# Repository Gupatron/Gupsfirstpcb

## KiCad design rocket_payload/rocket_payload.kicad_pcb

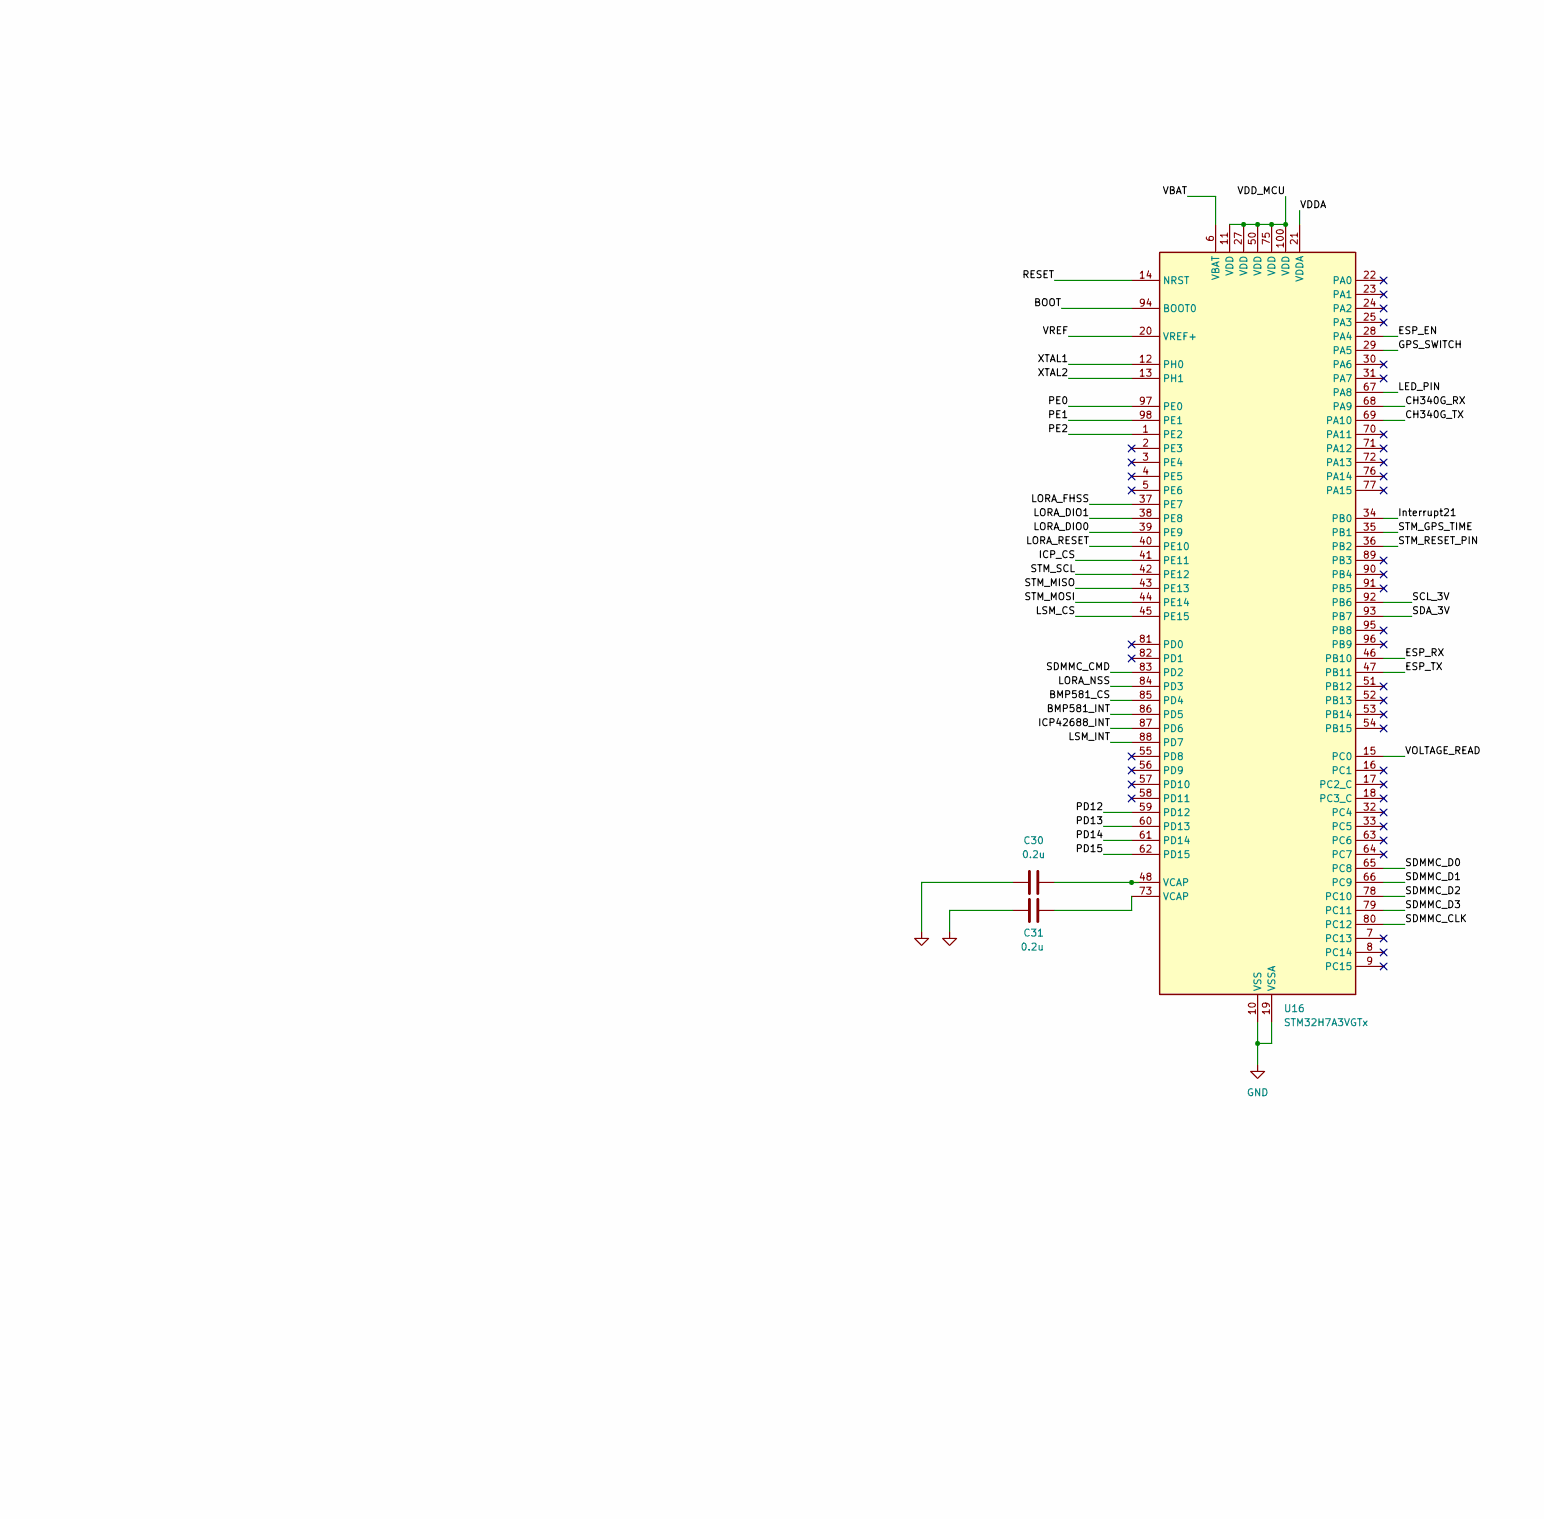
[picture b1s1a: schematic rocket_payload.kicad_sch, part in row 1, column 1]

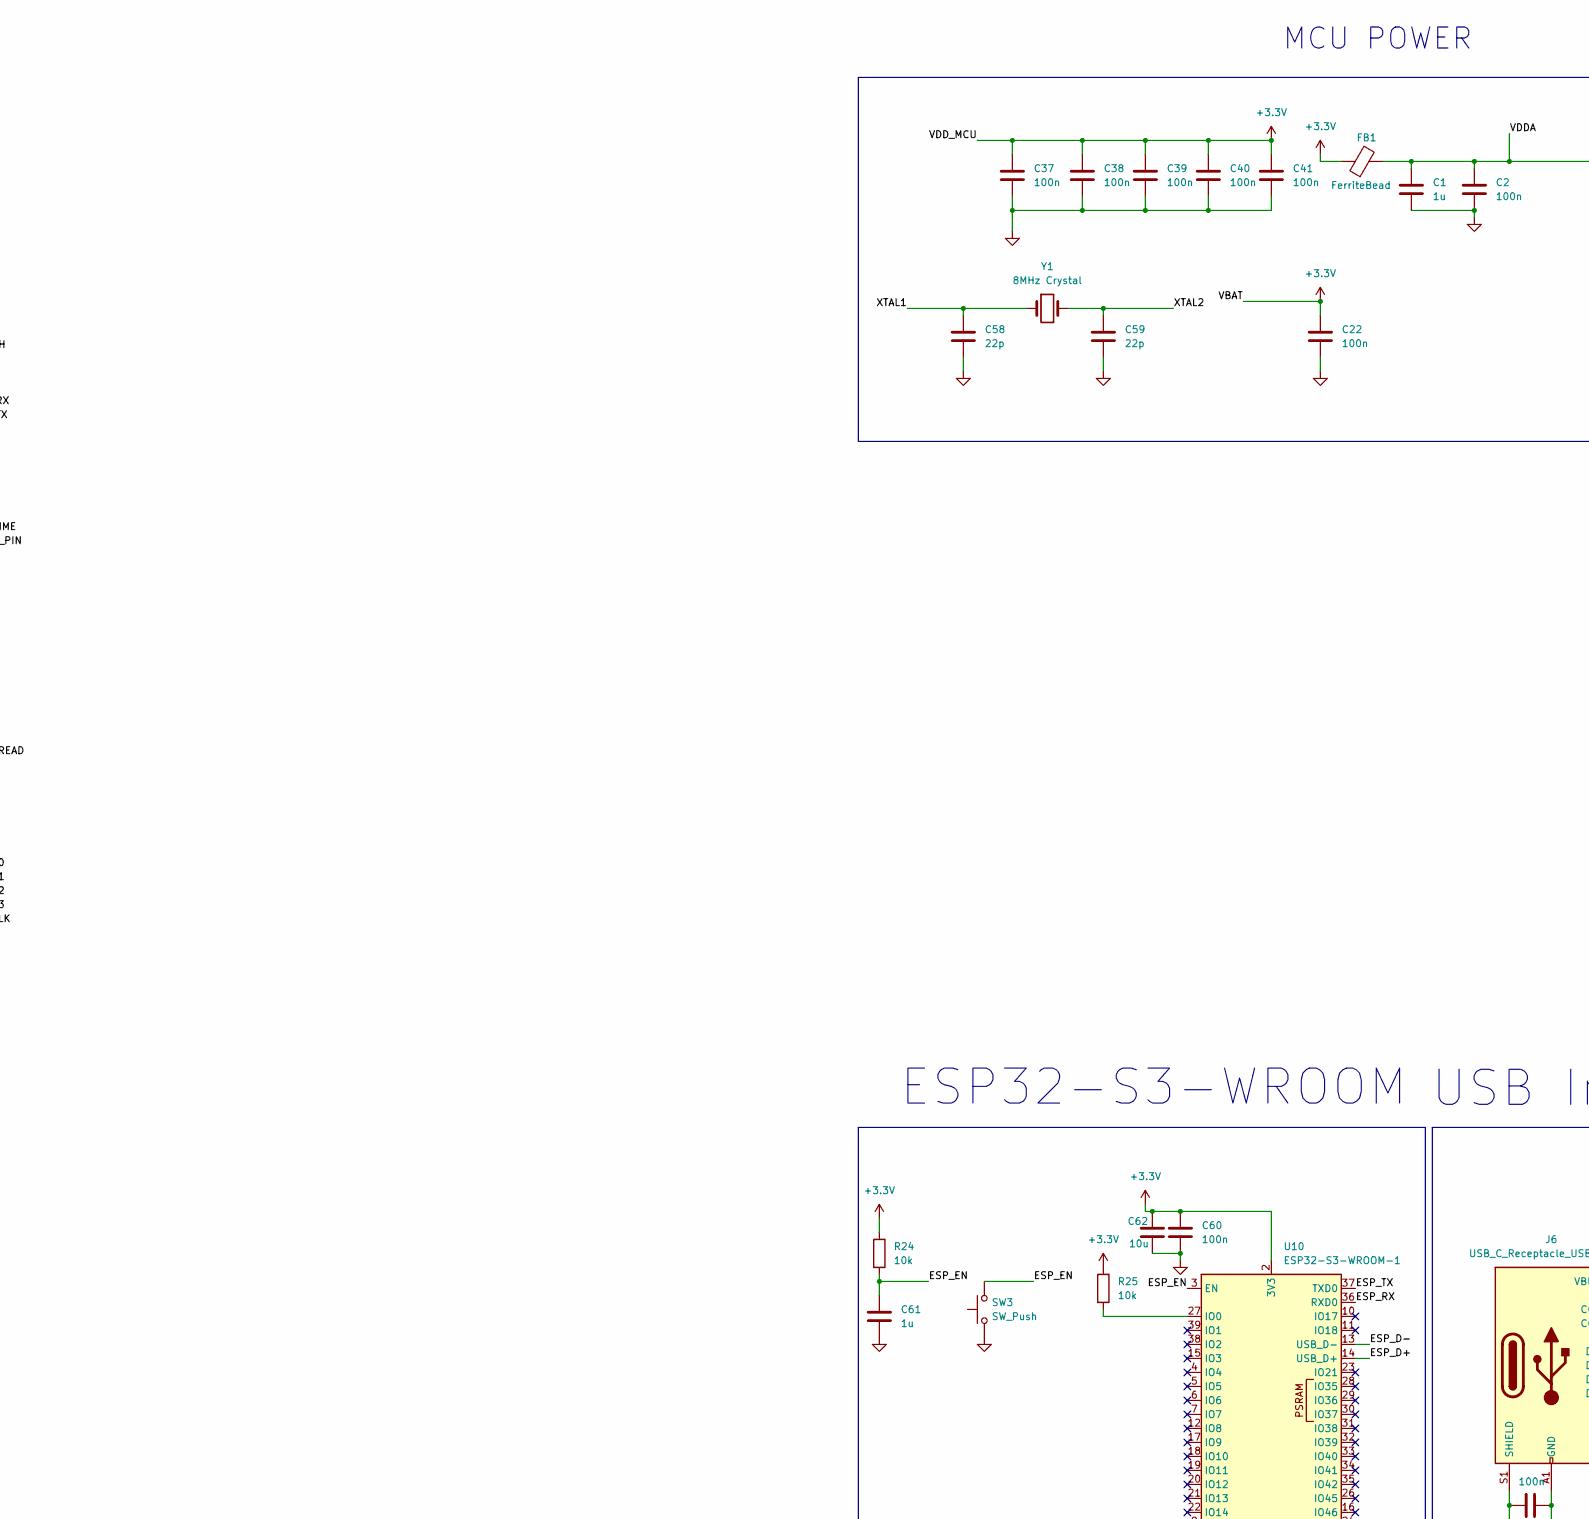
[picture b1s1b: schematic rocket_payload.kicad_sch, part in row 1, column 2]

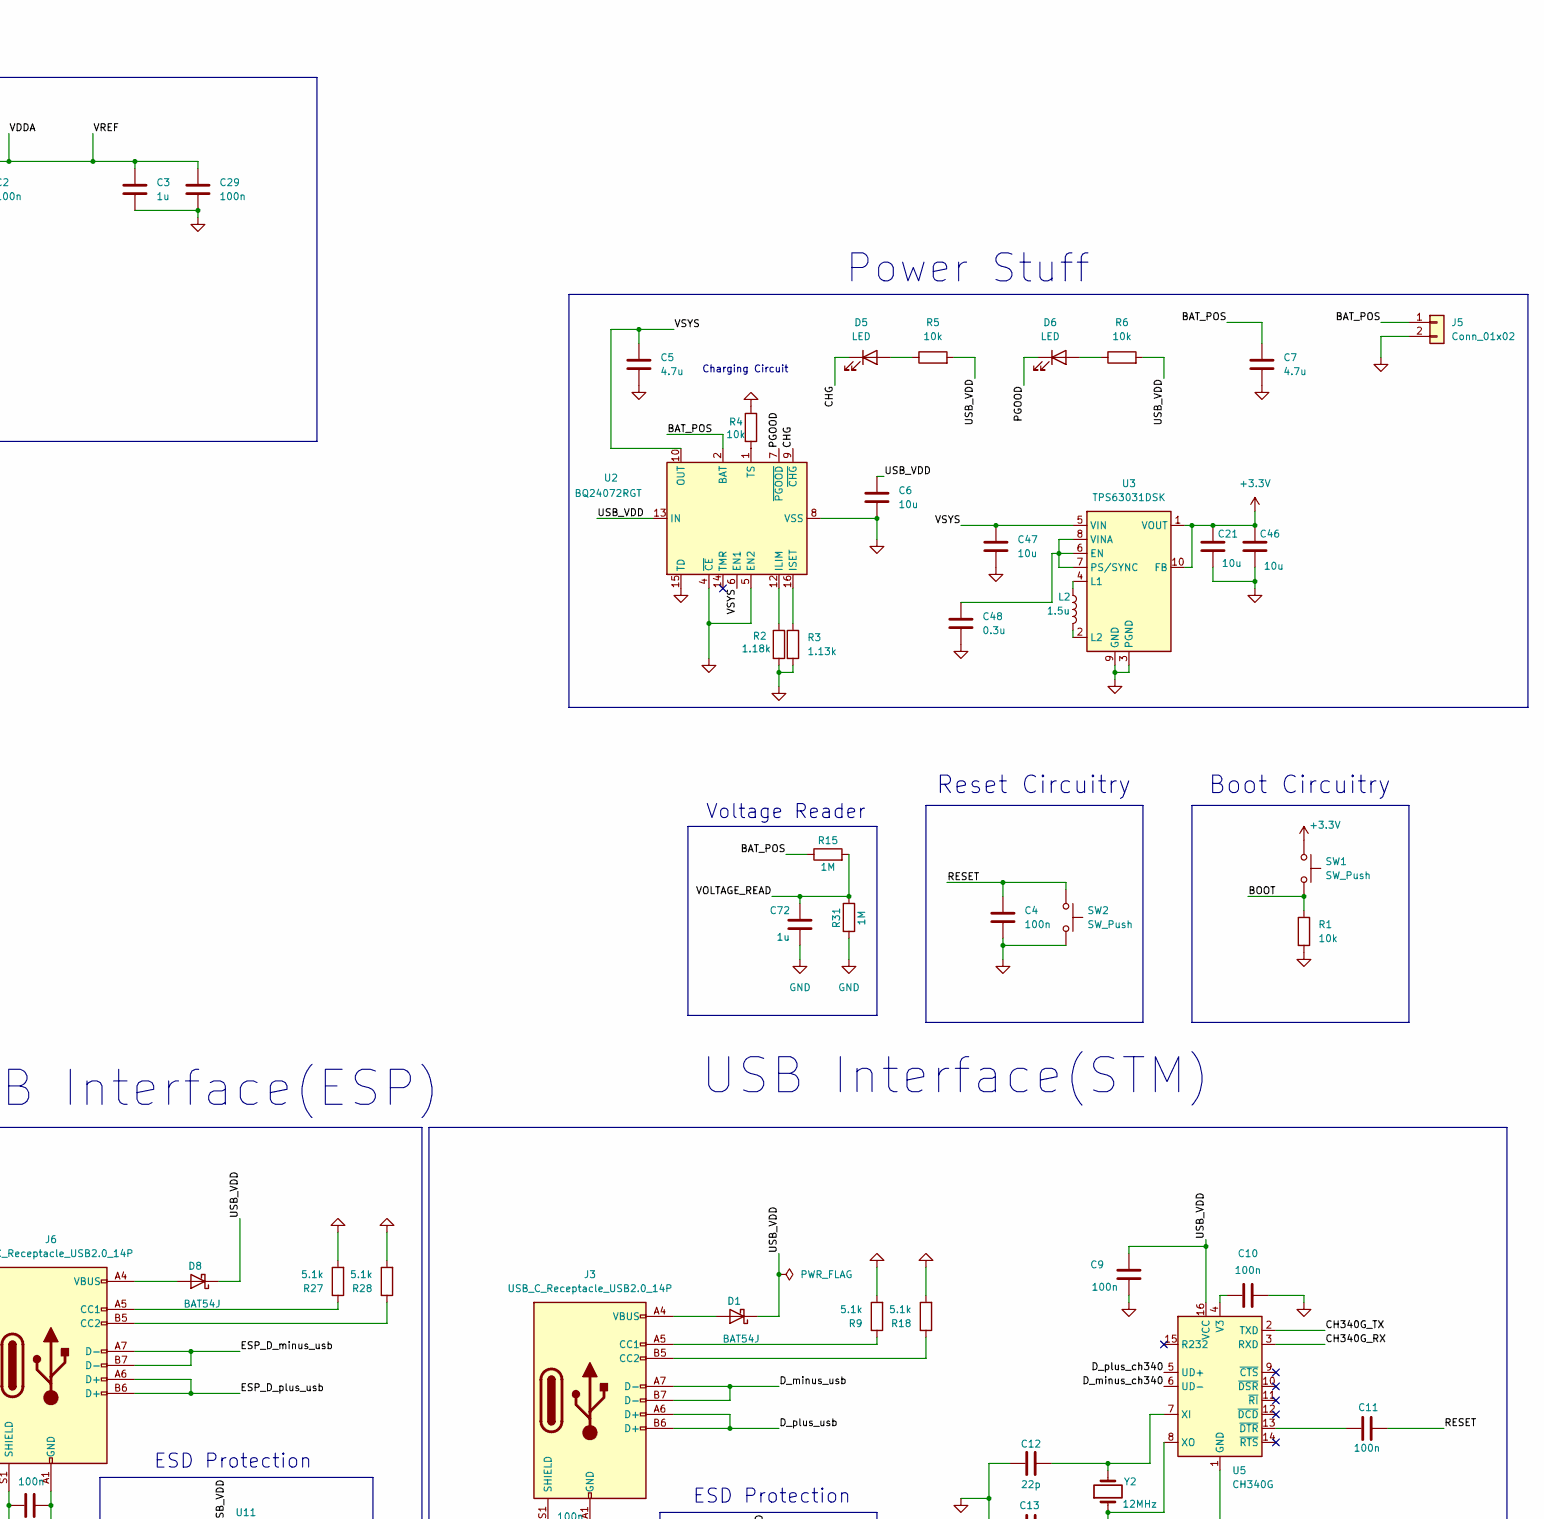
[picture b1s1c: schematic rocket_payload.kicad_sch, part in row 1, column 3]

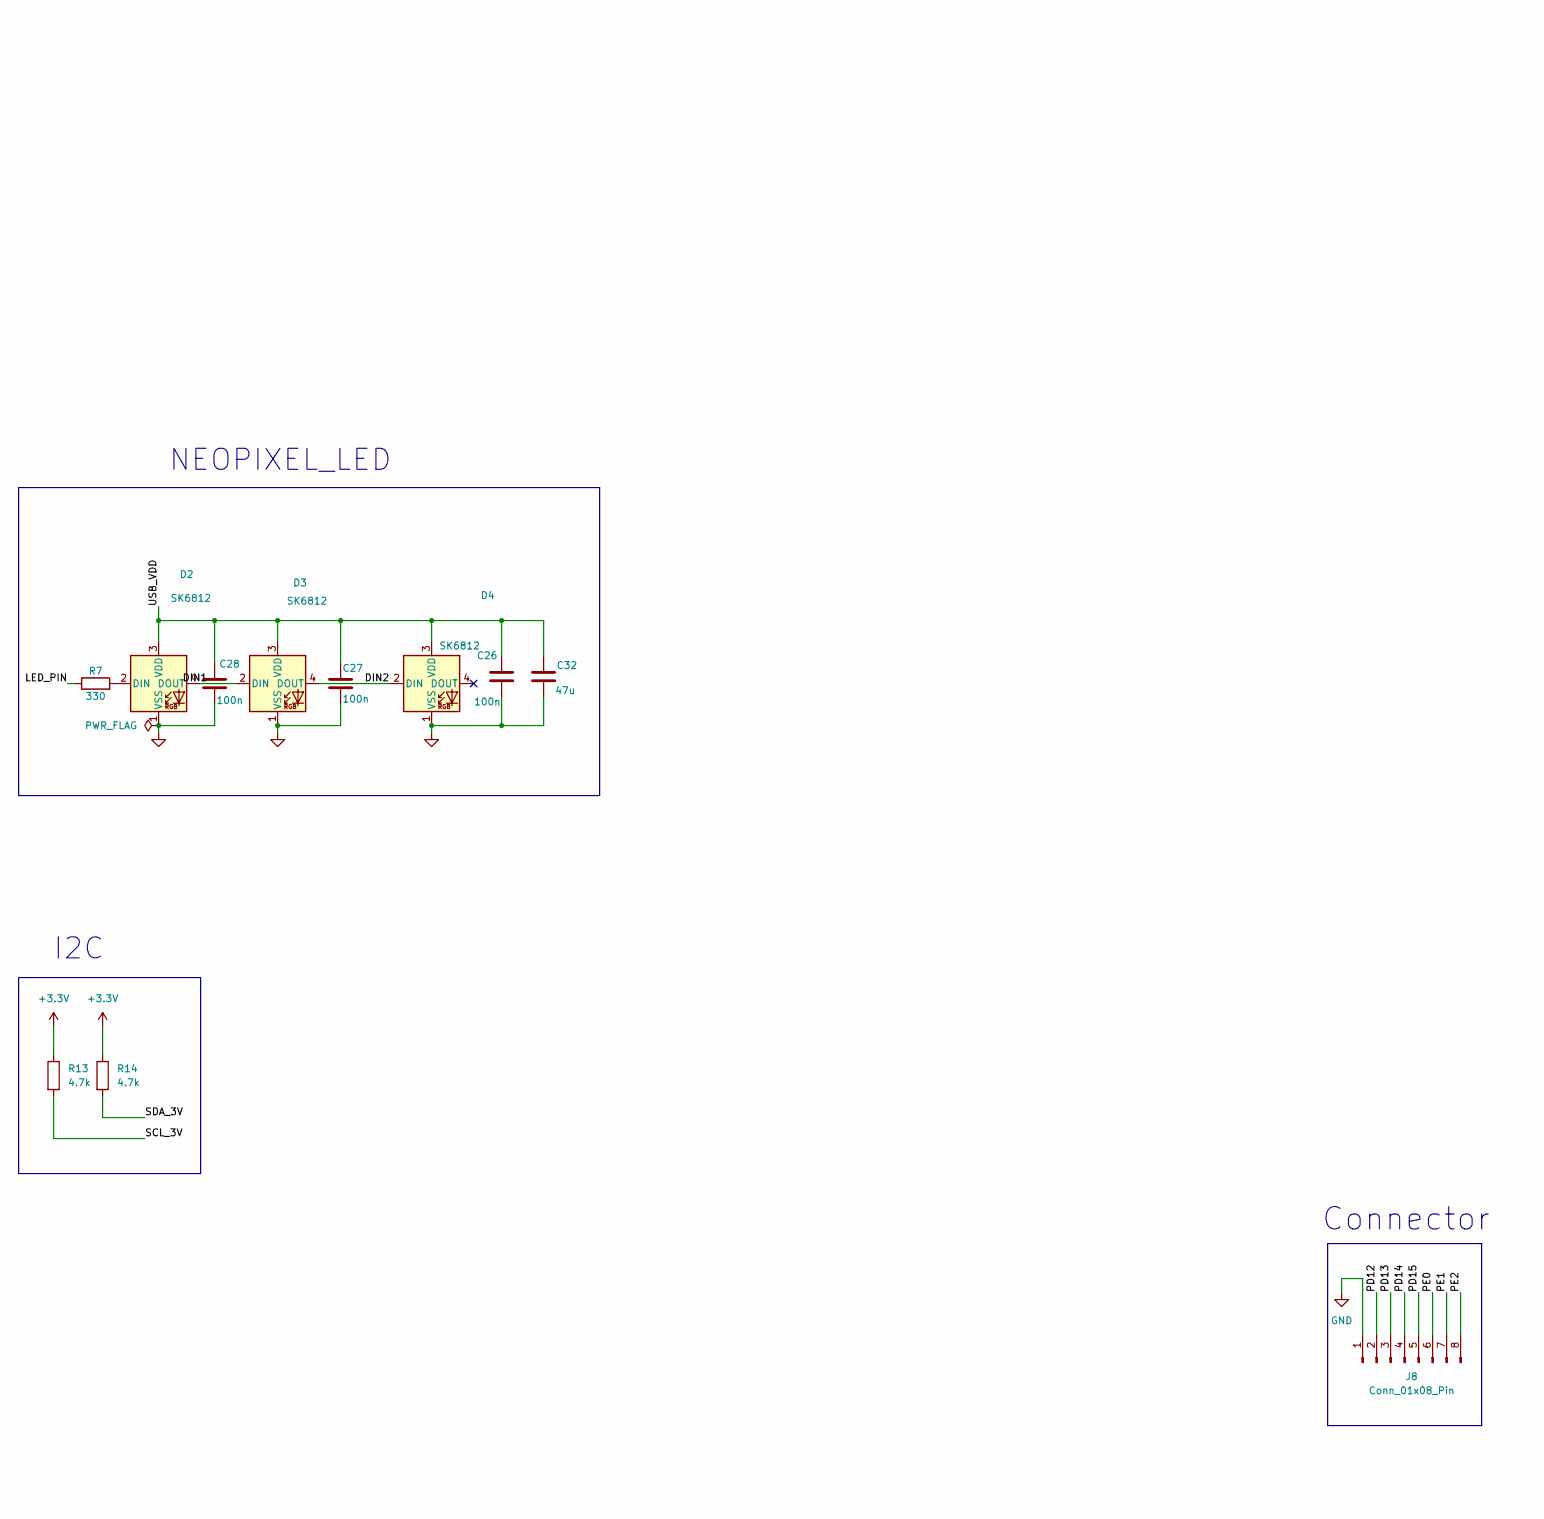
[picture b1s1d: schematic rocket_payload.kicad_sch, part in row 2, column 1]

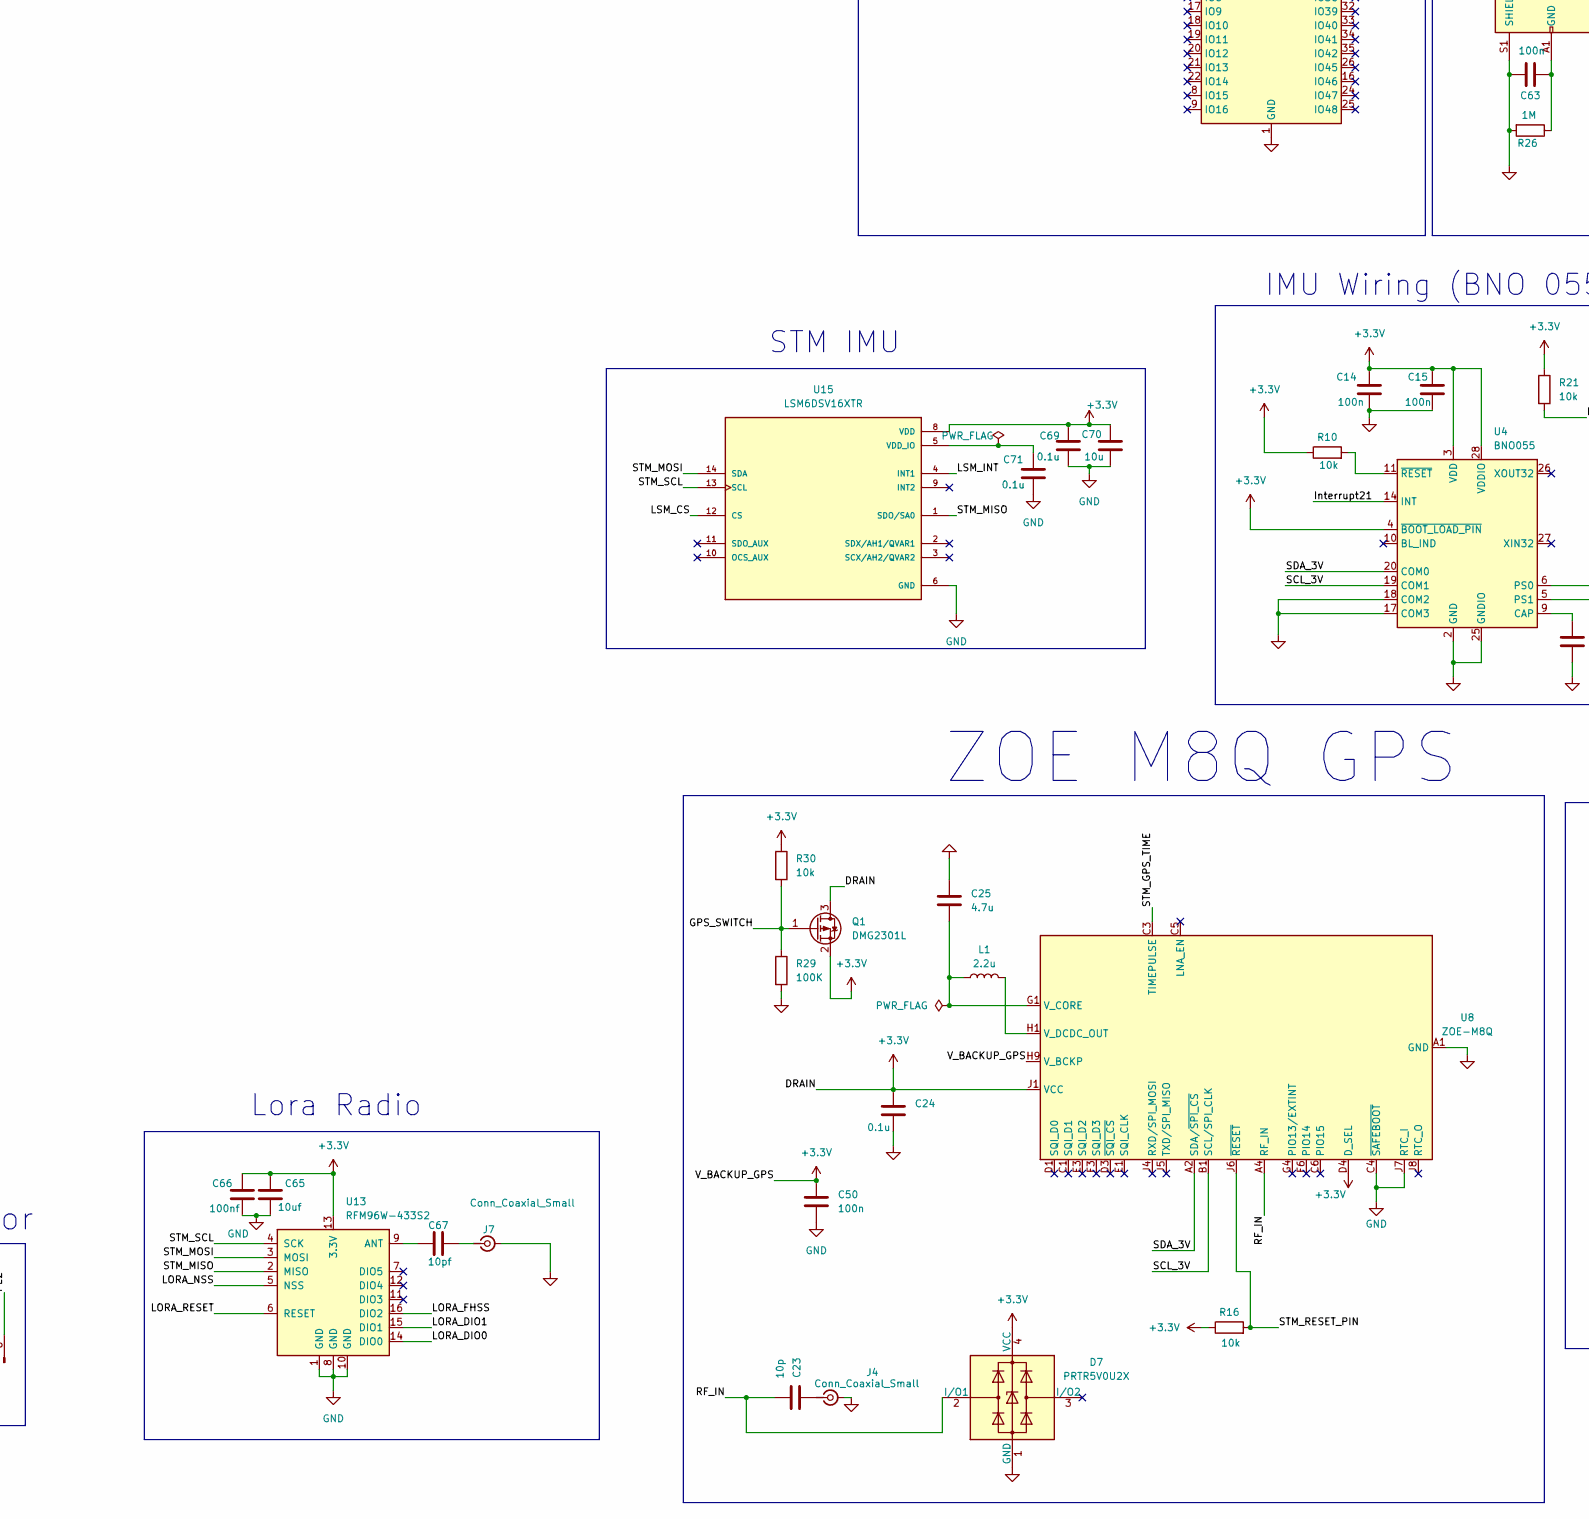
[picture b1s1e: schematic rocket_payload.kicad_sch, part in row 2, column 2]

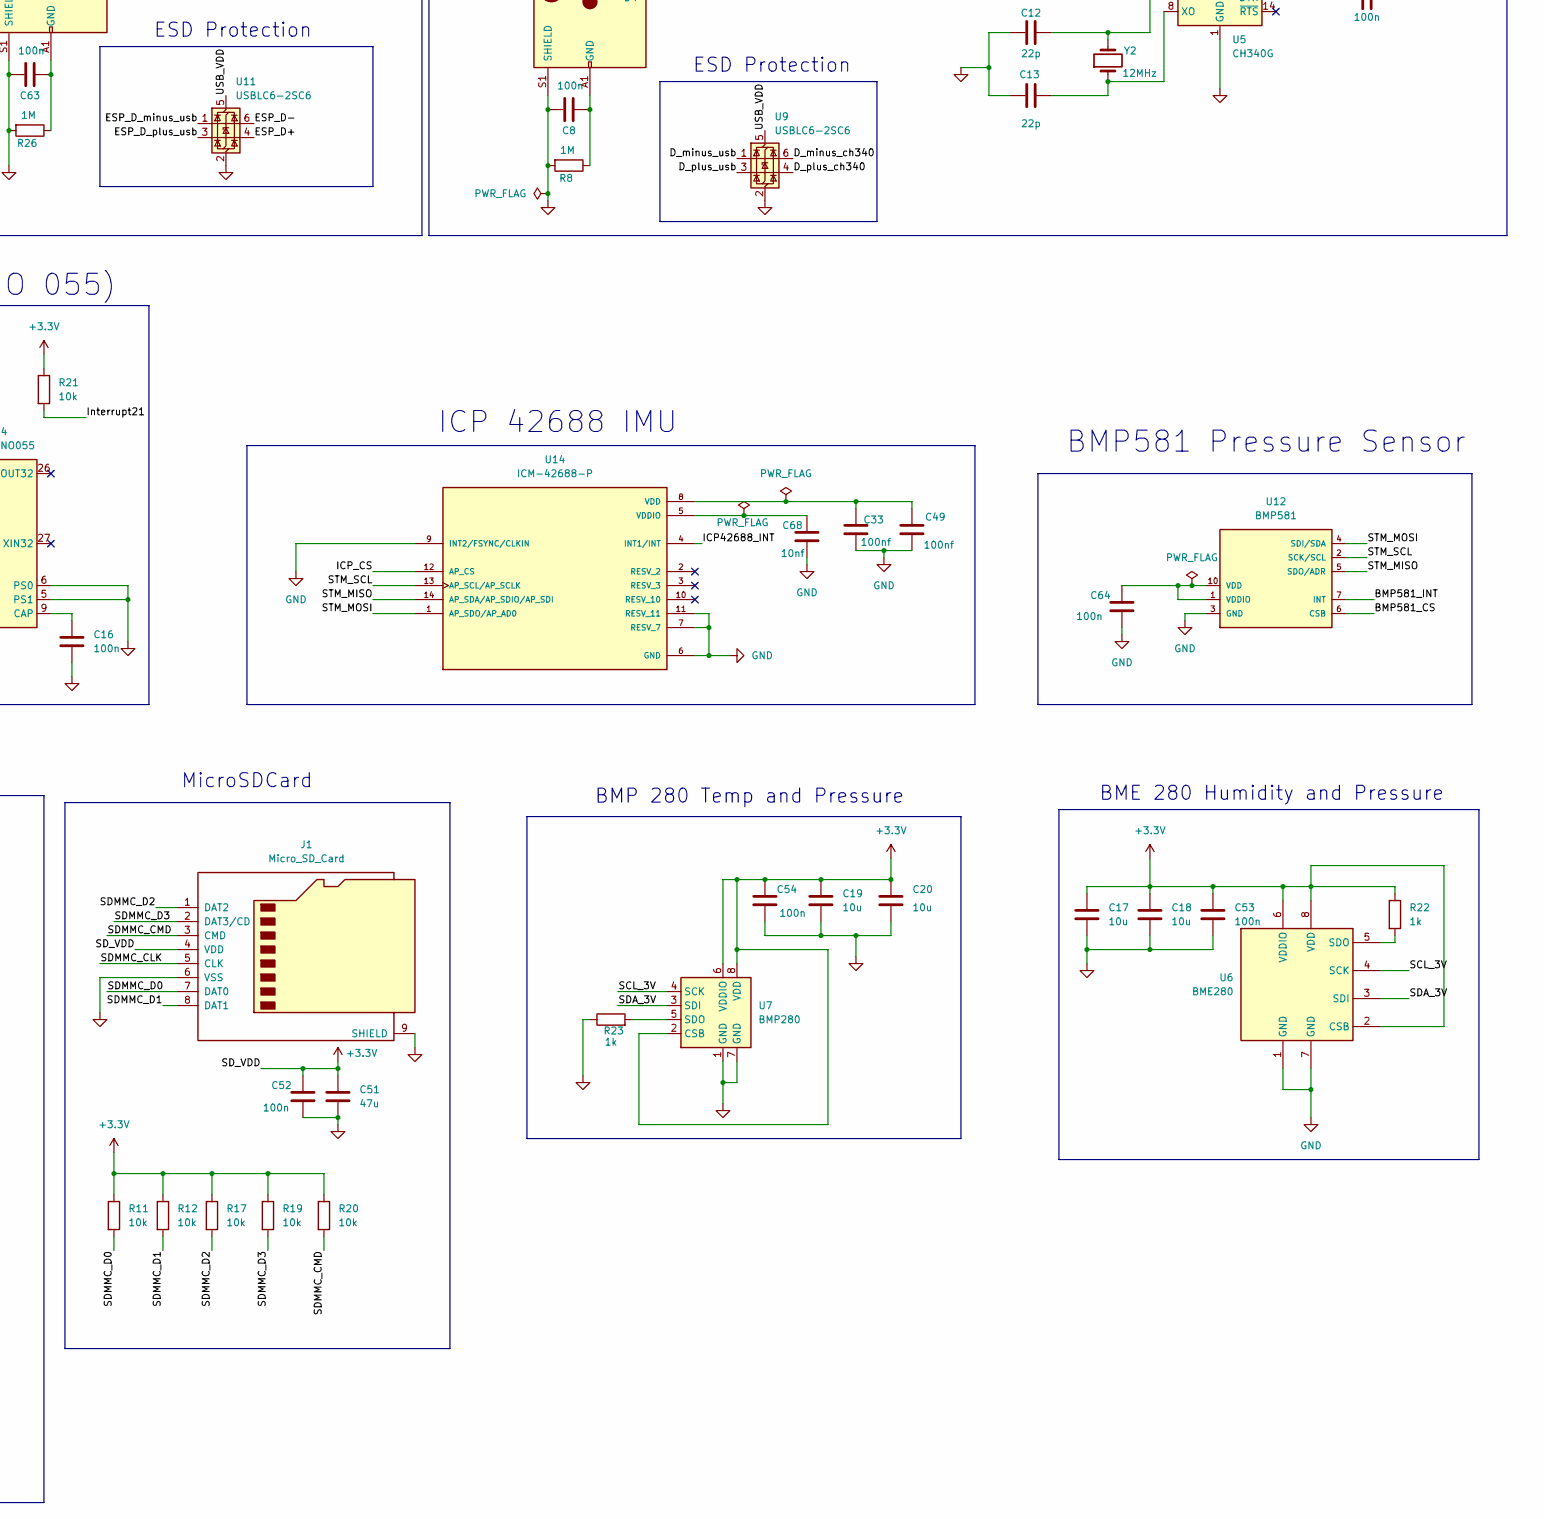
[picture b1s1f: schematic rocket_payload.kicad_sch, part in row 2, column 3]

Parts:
C1: 1u; C_0805_2012Metric
C2, C4, C8, C9, C10, C11, C14, C15, C16, C22, C26, C27, C28, C29, C37, C38, C39, C40, C41, C50, C52, C53, C54, C60, C63, C64: 100n; C_0402_1005Metric
C3, C61, C72: 1u; C_0402_1005Metric
C5, C7, C25: 4.7u; C_0805_2012Metric
C6, C17, C18, C19, C20, C21, C46, C47, C62: 10u; C_0805_2012Metric
C12, C13, C58, C59: 22p; C_0402_1005Metric
C23: 10p; C_0402_1005Metric
C24, C69, C71: 0.1u; C_0402_1005Metric
C30, C31: 0.2u; C_0402_1005Metric
C32, C51: 47u; C_1206_3216Metric
C33, C49, C66: 100nf; C_0402_1005Metric
C48: 0.3u; C_0402_1005Metric
C65: 10uf; C_0402_1005Metric
C67: 10pf; C_0402_1005Metric
C68: 10nf; C_0402_1005Metric
C70: 10u; C_0402_1005Metric
D1, D8: BAT54J; D_SOD-323F
D2, D3, D4: SK6812; LED_SK6812_PLCC4_5.0x5.0mm_P3.2mm
D5, D6: LED; LED_0402_1005Metric
D7: PRTR5V0U2X; SOT-143
FB1: FerriteBead; R_0402_1005Metric
J1: Micro_SD_Card; microSD_HC_Hirose_DM3AT-SF-PEJM5
J3, J6: USB_C_Receptacle_USB2.0_14P; USB_C_Receptacle_GCT_USB4085
J4, J7: Conn_Coaxial_Small; SMA_Amphenol_132289_EdgeMount
J5: Conn_01x02; JST_EH_S2B-EH_1x02_P2.50mm_Horizontal
J8: Conn_01x08_Pin; JST_EH_S8B-EH_1x08_P2.50mm_Horizontal
L1: 2.2u; L_0402_1005Metric
L2: 1.5u; L_0402_1005Metric
Q1: DMG2301L; SOT-23
R1, R4, R5, R6, R10, R11, R12, R16, R17, R19, R20, R21, R30: 10k; R_0402_1005Metric
R2: 1.18k; R_0402_1005Metric
R3: 1.13k; R_0402_1005Metric
R7: 330; R_0402_1005Metric
R8, R15, R26, R31: 1M; R_0402_1005Metric
R9, R18, R27, R28: 5.1k; R_0402_1005Metric
R13, R14: 4.7k; R_0402_1005Metric
R22, R23: 1k; R_0402_1005Metric
R24, R25: 10k; C_0402_1005Metric
R29: 100K; R_0402_1005Metric
SW1, SW2, SW3: SW_Push; Panasonic_EVQPUJ_EVQPUA
U2: BQ24072RGT; VQFN-16-1EP_3x3mm_P0.5mm_EP1.6x1.6mm
U3: TPS63031DSK; WSON-10-1EP_2.5x2.5mm_P0.5mm_EP1.2x2mm
U4: BNO055; LGA-28_5.2x3.8mm_P0.5mm
U5: CH340G; SOIC-16_3.9x9.9mm_P1.27mm
U6: BME280; Bosch_LGA-8_2.5x2.5mm_P0.65mm_ClockwisePinNumbering
U7: BMP280; Bosch_LGA-8_2x2.5mm_P0.65mm_ClockwisePinNumbering
U8: ZOE-M8Q; ublox_ZOE_M8
U9, U11: USBLC6-2SC6; SOT-23-6
U10: ESP32-S3-WROOM-1
U12: BMP581
U13: RFM96W-433S2; RFM9X-SMD
U14: ICM-42688-P; PQFN50P300X250X97-14N; PARTREV 1.2
U15: LSM6DSV16XTR; XDCR_LSM6DSV16XTR; PARTREV 4
U16: STM32H7A3VGTx; LQFP-100_14x14mm_P0.5mm
Y1: 8MHz Crystal; Crystal_SMD_3225-4Pin_3.2x2.5mm
Y2: 12MHz; Crystal_SMD_3225-4Pin_3.2x2.5mm

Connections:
/BAT_POS: C7.1, J5.1, R15.1, U2.2 (BAT), U2.3 (BAT)
/BMP581_CS: U12.6 (CSB), U16.85 (PD4)
/BMP581_INT: U12.7 (INT), U16.86 (PD5)
/BOOT: R1.1, SW1.2, U16.94 (BOOT0)
/CH340G_RX: U5.3 (RXD), U16.68 (PA9)
/CH340G_TX: U5.2 (TXD), U16.69 (PA10)
/CHG: D5.1 (K), U2.9 (~CHG)
/DIN1: D2.4 (DOUT), D3.2 (DIN)
/DIN2: D3.4 (DOUT), D4.2 (DIN)
/D_minus_ch340: U5.6 (UD-), U9.6 (I/O1)
/D_minus_usb: J3.A7 (D-), J3.B7 (D-), U9.1 (I/O1)
/D_plus_ch340: U5.5 (UD+), U9.4 (I/O2)
/D_plus_usb: J3.A6 (D+), J3.B6 (D+), U9.3 (I/O2)
/ESP_D+: U10.14 (USB_D+), U11.4 (I/O2)
/ESP_D-: U10.13 (USB_D-), U11.6 (I/O1)
/ESP_D_minus_usb: J6.A7 (D-), J6.B7 (D-), U11.1 (I/O1)
/ESP_D_plus_usb: J6.A6 (D+), J6.B6 (D+), U11.3 (I/O2)
/ESP_EN: C61.1, R24.2, SW3.2, U10.3 (EN), U16.28 (PA4)
/ESP_RX: U10.36 (RXD0), U16.46 (PB10)
/ESP_TX: U10.37 (TXD0), U16.47 (PB11)
/GPS_SWITCH: Q1.1 (G), R29.1, R30.2, U16.29 (PA5)
/ICP42688_INT: U14.4 (INT1/INT), U16.87 (PD6)
/ICP_CS: U14.12 (AP_CS), U16.41 (PE11)
/Interrupt21: R21.2, U4.14 (INT), U16.34 (PB0)
/LED_PIN: R7.1, U16.67 (PA8)
/LORA_DIO0: U13.14 (DIO0), U16.39 (PE9)
/LORA_DIO1: U13.15 (DIO1), U16.38 (PE8)
/LORA_FHSS: U13.16 (DIO2), U16.37 (PE7)
/LORA_NSS: U13.5 (NSS), U16.84 (PD3)
/LORA_RESET: U13.6 (RESET), U16.40 (PE10)
/LSM_CS: U15.12 (CS), U16.45 (PE15)
/LSM_INT: U15.4 (INT1), U16.88 (PD7)
/PD12: J8.2, U16.59 (PD12)
/PD13: J8.3, U16.60 (PD13)
/PD14: J8.4, U16.61 (PD14)
/PD15: J8.5, U16.62 (PD15)
/PE0: J8.6, U16.97 (PE0)
/PE1: J8.7, U16.98 (PE1)
/PE2: J8.8, U16.1 (PE2)
/PGOOD: D6.1 (K), U2.7 (~PGOOD)
/RESET: C4.1, C11.2, SW2.1, U16.14 (NRST)
/RF_IN: C23.2, D7.2 (I/O1), U8.A4 (RF_IN)
/SCL_3V: R13.2, U4.19 (COM1), U6.4 (SCK), U7.4 (SCK), U8.B1 (SCL/SPI_CLK), U16.92 (PB6)
/SDA_3V: R14.2, U4.20 (COM0), U6.3 (SDI), U7.3 (SDI), U8.A2 (SDA/~SPI_CS), U16.93 (PB7)
/SDMMC_CLK: J1.5 (CLK), U16.80 (PC12)
/SDMMC_CMD: J1.3 (CMD), R20.2, U16.83 (PD2)
/SDMMC_D0: J1.7 (DAT0), R11.2, U16.65 (PC8)
/SDMMC_D1: J1.8 (DAT1), R12.2, U16.66 (PC9)
/SDMMC_D2: J1.1 (DAT2), R17.2, U16.78 (PC10)
/SDMMC_D3: J1.2 (DAT3/CD), R19.2, U16.79 (PC11)
/STM_GPS_TIME: U8.C3 (TIMEPULSE), U16.35 (PB1)
/STM_MISO: U12.5 (SDO/ADR), U13.2 (MISO), U14.14 (AP_SDA/AP_SDIO/AP_SDI), U15.1 (SDO/SA0), U16.43 (PE13)
/STM_MOSI: U12.4 (SDI/SDA), U13.3 (MOSI), U14.1 (AP_SDO/AP_AD0), U15.14 (SDA), U16.44 (PE14)
/STM_RESET_PIN: R16.2, U8.J6 (~RESET), U16.36 (PB2)
/STM_SCL: U12.2 (SCK/SCL), U13.4 (SCK), U14.13 (AP_SCL/AP_SCLK), U15.13 (SCL), U16.42 (PE12)
/USB_VDD: C6.1, C9.1, C26.1, C27.1, C28.1, C32.1, D1.1 (K), D2.3 (VDD), D3.3 (VDD), D4.3 (VDD), D8.1 (K), R5.2, R6.2, U2.13 (IN), U5.16 (VCC), U9.5 (VBUS), U11.5 (VBUS)
/VDDA: C1.1, C2.1, C3.1, C29.1, FB1.2, U16.20 (VREF+), U16.21 (VDDA)
/VOLTAGE_READ: C72.1, R15.2, R31.1, U16.15 (PC0)
/VSYS: C5.1, C47.1, U2.6 (EN1), U2.10 (OUT), U2.11 (OUT), U3.5 (VIN)
/XTAL1: C58.1, U16.12 (PH0), Y1.1
/XTAL2: C59.1, U16.13 (PH1), Y1.2
<NO NET>: C8.2, C63.2, J3.S1 (SHIELD), J6.S1 (SHIELD), R8.2, R26.2
GND: C1.2, C2.2, C3.2, C4.2, C5.2, C6.2, C7.2, C9.2, C10.2, C12.1, C13.1, C14.2, C15.2, C16.2, C17.2, C18.2, C19.2, C20.2, C21.2, C22.2, C24.2, C25.1, C26.2, C27.2, C28.2, C29.2, C30.1, C31.1, C32.2, C33.2, C37.2, C38.2, C39.2, C40.2, C41.2, C46.2, C47.2, C48.2, C49.2, C50.2, C51.2, C52.2, C53.2, C54.2, C58.2, C59.2, C60.2, C61.2, C62.2, C64.2, C65.2, C66.2, C68.2, C69.2, C70.2, C71.2, C72.2, D2.1 (VSS), D3.1 (VSS), D4.1 (VSS), D7.1 (GND), J1.6 (VSS), J1.9 (SHIELD), J4.2 (Ext), J5.2, J7.2 (Ext), J8.1, R1.2, R2.2, R3.2, R4.1, R9.2, R18.2, R23.1, R27.2, R28.2, R29.2, R31.2, SW2.2, SW3.1, U2.4 (~CE), U2.5 (EN2), U2.8 (VSS), U2.15 (TD), U2.17 (VSS), U3.3 (PGND), U3.9 (GND), U3.11 (PGND), U4.2 (GND), U4.5 (PS1), U4.6 (PS0), U4.17 (COM3), U4.18 (COM2), U4.25 (GNDIO), U5.1 (GND), U6.1 (GND), U6.7 (GND), U7.1 (GND), U7.7 (GND), U8.A1 (GND), U8.A3 (GND), U8.A5 (GND), U8.A7 (GND), U8.A8 (GND), U8.A9 (GND), U8.B9 (GND), U8.C4 (~SAFEBOOT), U8.C7 (GND), U8.C9 (GND), U8.D6 (GND), U8.D9 (GND), U8.E7 (GND), U8.F7 (GND), U8.G3 (GND), U8.G6 (GND), U8.G7 (GND), U8.J3 (GND), U8.J7 (RTC_I), U8.J9 (GND), U9.2 (GND), U10.1 (GND), U10.40 (GND), U10.41 (GND), U11.2 (GND), U12.3 (GND), U12.8 (GND), U12.9 (GND), U13.1 (GND), U13.8 (GND), U13.10 (GND), U14.6 (GND), U14.7 (RESV_7), U14.9 (INT2/FSYNC/CLKIN), U14.11 (RESV_11), U15.6 (GND), U15.7 (GND), U16.10 (VSS), U16.19 (VSSA), U16.26 (VSS), U16.49 (VSS), U16.74 (VSS), U16.99 (VSS); also elsewhere on the board
unnamed: C8.1, J3.A1 (GND), J3.A12 (GND), J3.B1 (GND), J3.B12 (GND), R8.1
unnamed: C30.2, U16.48 (VCAP)
unnamed: C31.2, U16.73 (VCAP)
unnamed: C63.1, J6.A1 (GND), J6.A12 (GND), J6.B1 (GND), J6.B12 (GND), R26.1
unnamed: D1.2 (A), J3.A4 (VBUS), J3.A9 (VBUS), J3.B4 (VBUS), J3.B9 (VBUS)
unnamed: D2.2 (DIN), R7.2
unnamed: D5.2 (A), R5.1
unnamed: D6.2 (A), R6.1
unnamed: D8.2 (A), J6.A4 (VBUS), J6.A9 (VBUS), J6.B4 (VBUS), J6.B9 (VBUS)
unnamed: J3.A5 (CC1), R9.1
unnamed: J3.B5 (CC2), R18.1
unnamed: C23.1, J4.1 (In)
unnamed: J6.A5 (CC1), R27.1
unnamed: J6.B5 (CC2), R28.1
unnamed: C67.2, J7.1 (In)
unnamed: R2.1, U2.12 (ILIM)
unnamed: R3.1, U2.16 (ISET)
unnamed: R4.2, U2.1 (TS)
unnamed: C48.1, U3.6 (EN), U3.7 (PS/SYNC), U3.8 (VINA)
unnamed: L2.1, U3.4 (L1)
unnamed: L2.2, U3.2 (L2)
unnamed: C16.1, U4.9 (CAP)
unnamed: R10.2, U4.11 (~RESET)
unnamed: C10.1, U5.4 (V3)
unnamed: C12.2, U5.7 (XI), Y2.2
unnamed: C13.2, U5.8 (XO), Y2.1
unnamed: C11.1, U5.13 (~DTR)
unnamed: R22.2, U6.5 (SDO)
unnamed: R23.2, U7.5 (SDO)
unnamed: C25.2, L1.1, U8.G1 (V_CORE)
unnamed: L1.2, U8.H1 (V_DCDC_OUT)
unnamed: R25.2, U10.27 (IO0)
unnamed: C64.1, U12.1 (VDDIO), U12.10 (VDD)
unnamed: C67.1, U13.9 (ANT)
unnamed: C68.1, U14.5 (VDDIO)
unnamed: C71.1, U15.5 (VDD_IO)

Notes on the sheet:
BME 280 Humidity and Pressure
MCU POWER
ICP 42688 IMU
USB Interface(STM)
Charging Circuit
Voltage Reader
BMP581 Pressure Sensor
Connector
I2C
ESD Protection
Boot Circuitry
MicroSDCard
USB Interface(ESP)
BMP 280 Temp and Pressure
STM IMU
Power Stuff
ZOE M8Q GPS
ESP32-S3-WROOM
IMU Wiring (BNO 055)
Lora Radio
Reset Circuitry
NEOPIXEL_LED

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
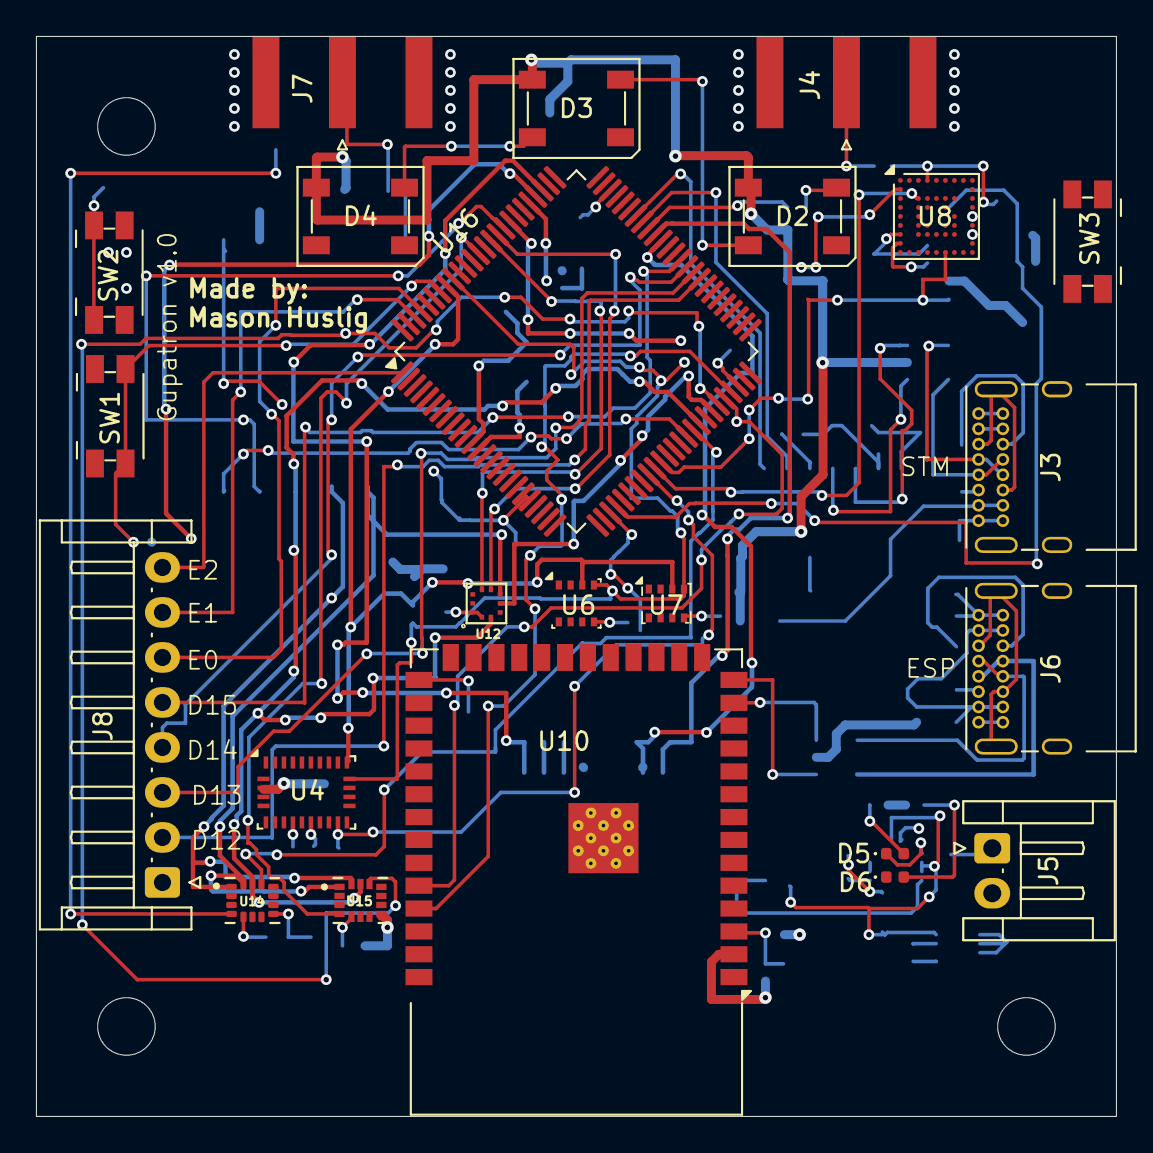
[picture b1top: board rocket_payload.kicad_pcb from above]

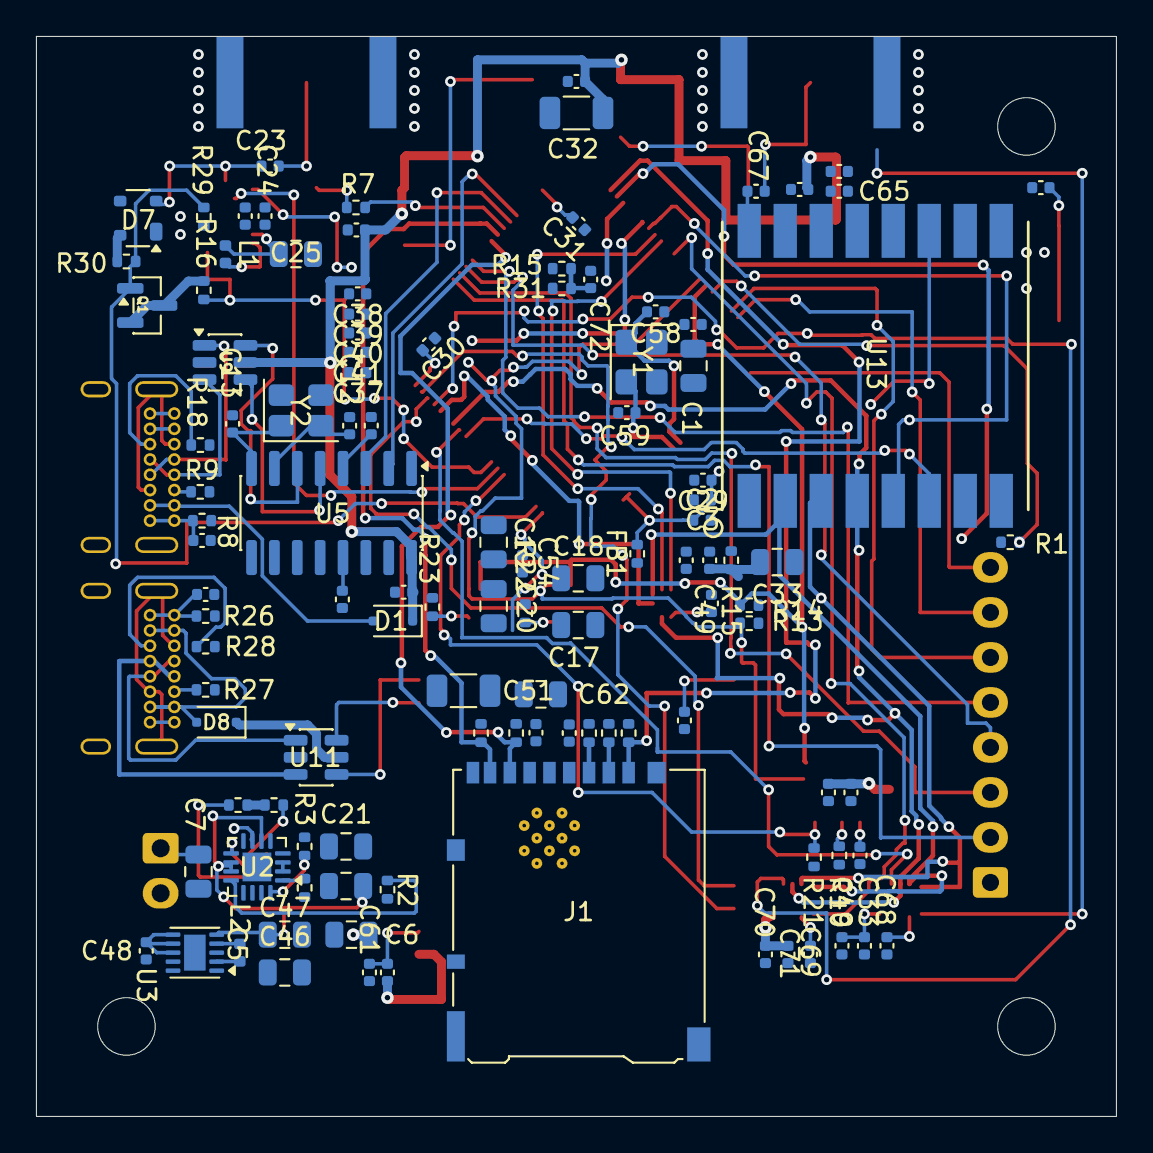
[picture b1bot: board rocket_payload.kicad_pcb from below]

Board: 4 copper layers, 60.0 x 60.0 mm, 135 parts (112 on the bottom side), 101 nets.

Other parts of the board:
C33#2, C49#2: 100nf; C_0402_1005Metric
R15#2: 10k; R_0402_1005Metric

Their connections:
GND: C33#2.2, C49#2.2; also elsewhere on the board

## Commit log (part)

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2026-02-17 schematic halfway done?
2026-05-24 added changes
2026-05-24 finished schematic
2026-05-24 did erc and now schematic is fin
2026-05-24 added footprints
2026-05-25 routing
2026-05-26 added esp
2026-05-29 located all components
